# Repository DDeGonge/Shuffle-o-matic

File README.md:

# Shuffle-o-matic

Full overview video:
https://www.youtube.com/watch?v=eMTXyl7tPEk

Thingiverse page (cad files):
https://www.thingiverse.com/thing:4547302

## Significant experience recommended if you want to take on this project, it isn't documented very well :)

Hardware required
|Qty|Item|Supplier||
|---|---|---|---|
| | 3D printed Parts | |
| 3 | Nema 17 stepper motors, <=40mm long | [17HS15-1504S-X1 39mm long](https://www.aliexpress.com/item/1005002191787745.html?spm=2114.12010612.8148356.4.2bca2904n3VYBm)|
| 5 | Gates GT2 20t idlers with standoffs | |
| 3 | Gates GT2 20t drive pulleys | |
| 1 | MG90S servo | [MG90S servo](https://ebay.us/60Pxun) |
| 1 | 600rpm micro gearbox motor | [DC 3V 6V 12V GA12-N20](https://www.aliexpress.com/item/4000274747864.html?spm=a2g0o.productlist.0.0.63e42e07j3CYN8&algo_pvid=cd6ee419-621c-4ffe-9044-3ffd2ae1bfeb&algo_expid=cd6ee419-621c-4ffe-9044-3ffd2ae1bfeb-0&btsid=0bb0623a16150221042227975ecf2c&ws_ab_test=searchweb0_0,searchweb201602_,searchweb201603_)|
| 2 | MGN9 linear profile bearings, 135mm len | [MGN9C](https://www.aliexpress.com/item/32773296501.html?spm=a2g0o.cart.0.0.54873c00SIeLte&mp=1) |
| 1 | MGN9 linear profile bearing, 95mm len | [MGN9C](https://www.aliexpress.com/item/32773296501.html?spm=a2g0o.cart.0.0.54873c00SIeLte&mp=1) |
| 6 | 6700 bearing | [6700ZZ](https://www.aliexpress.com/item/32852057465.html?spm=a2g0o.cart.0.0.54873c00SIeLte&mp=1) |
| 1 | Raspberry Pi | |
| 1 | (optional) Raspberry Pi Camera V1.4 | |
| 1 | (optional) 3x 3mm white led | |
| 1 | Adafruit Feather | |
| 1 | Breadboard/pcb for laying out components | |
| ~ | Assorted M2 and M3 nuts and bolts | |

All part numbers in the pcb should be accurate, though again review and order at your own risk. Use KiCad to view/edit, it's free!

And probably a few other things I'm forgetting. Seriously if you want to make this, do so at your own risk. Review the cad model yourself and make sure you have everything accounted for! This is not a project for beginners!

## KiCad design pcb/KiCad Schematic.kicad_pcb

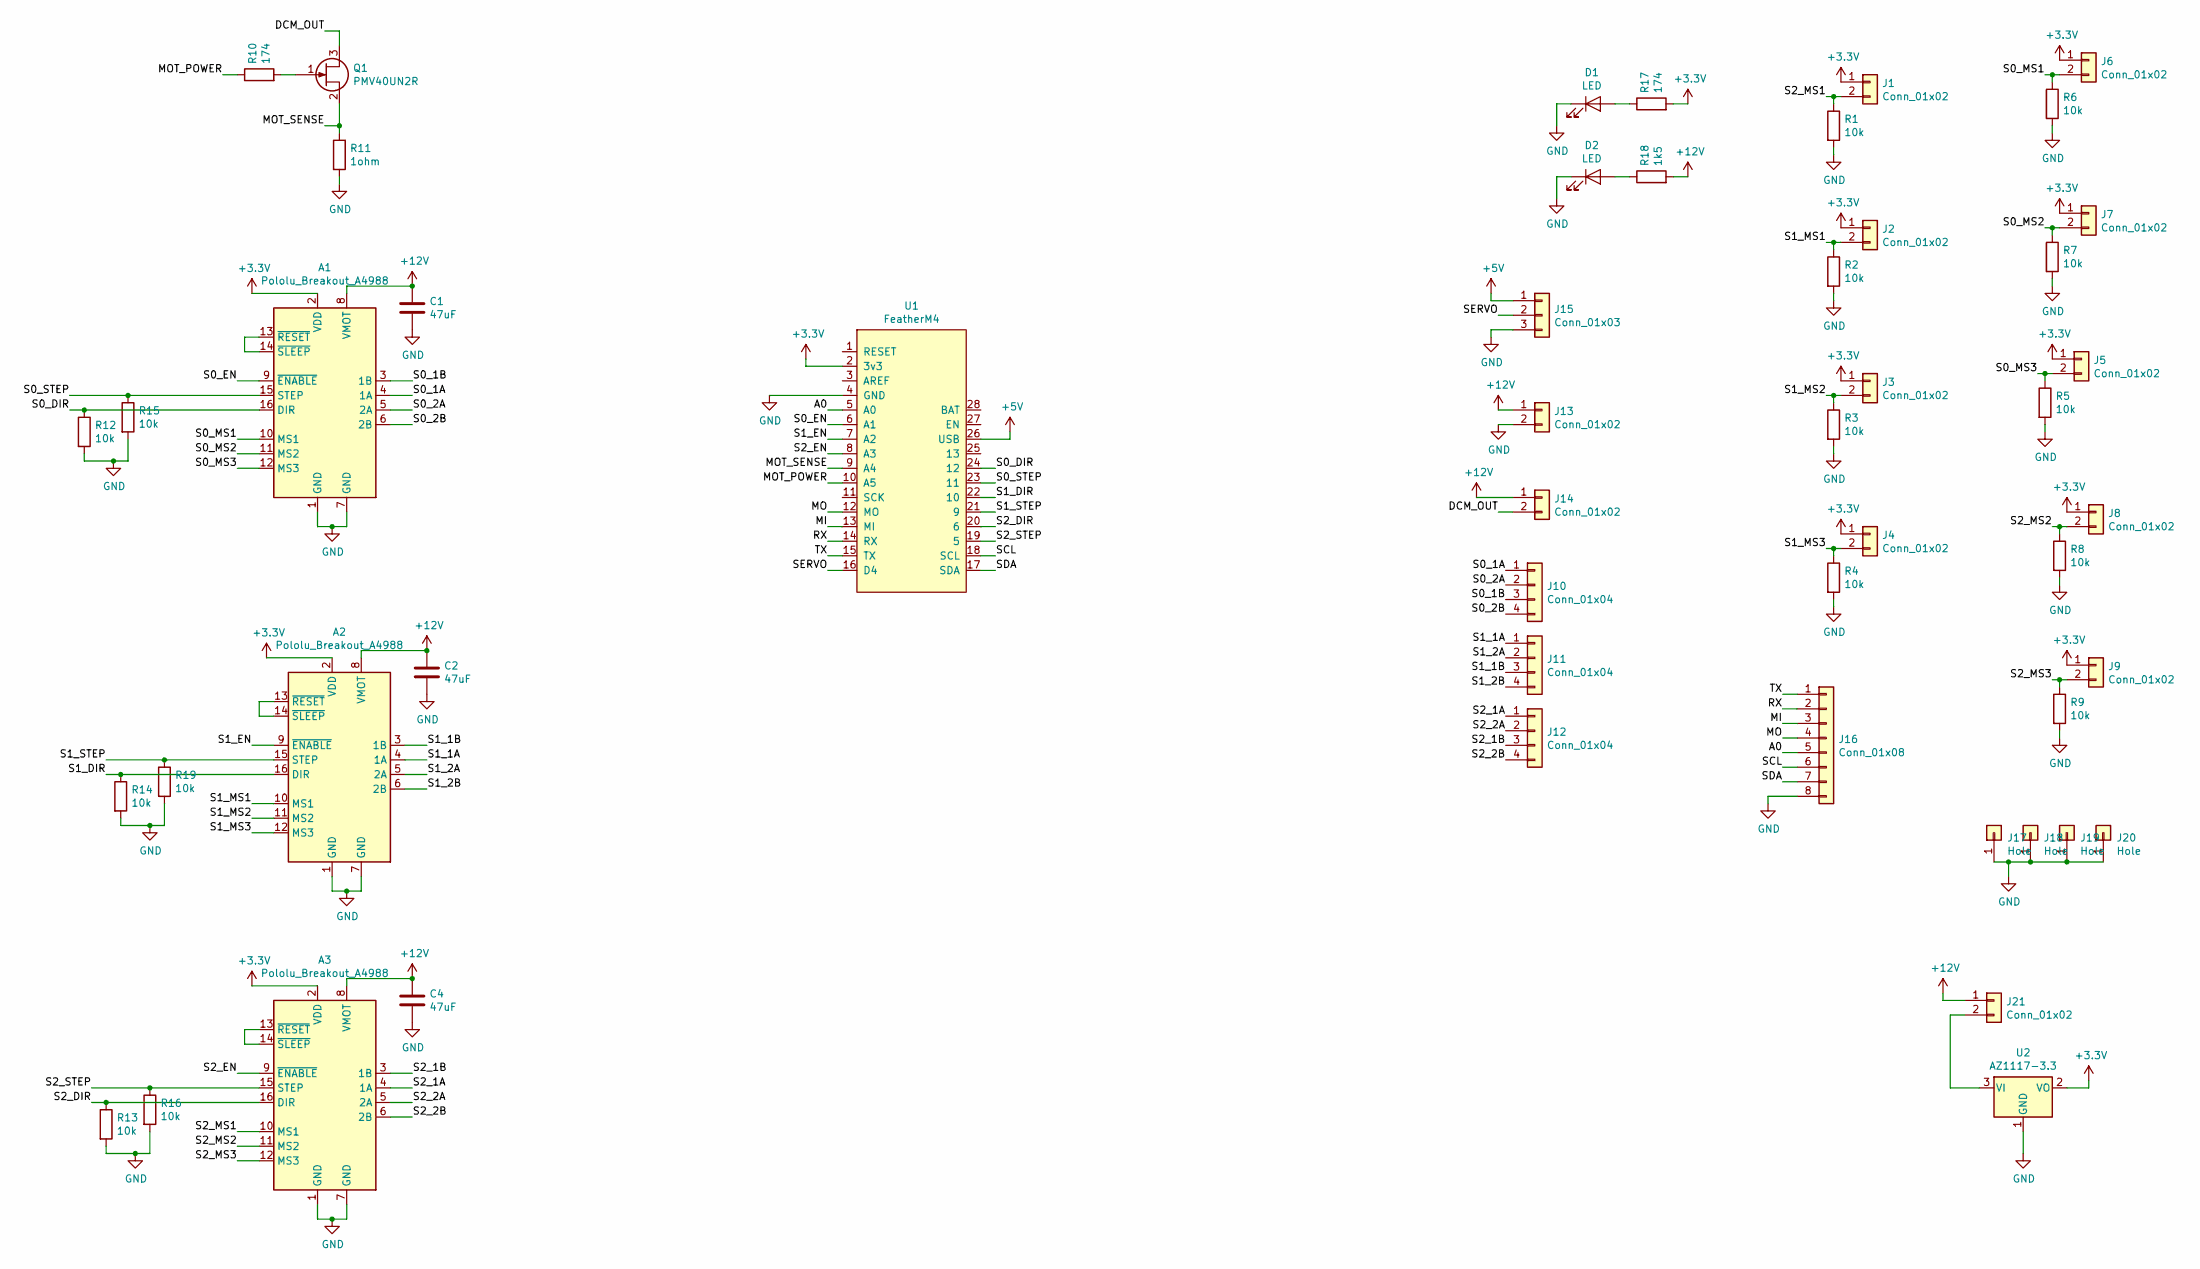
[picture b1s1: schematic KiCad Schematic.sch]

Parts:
A1, A2, A3: Pololu_Breakout_A4988; Pololu_Breakout-16_15.2x20.3mm
C1, C2, C4: 47uF; CP_Elec_6.3x5.8
D1, D2: LED; LED_0603_1608Metric
J1, J2, J3, J4, J5, J6, J7, J8, J9, J14, J21: Conn_01x02; PinHeader_1x02_P2.54mm_Vertical
J10, J11, J12: Conn_01x04; PinSocket_1x04_P2.54mm_Vertical
J13: Conn_01x02; BarrelJack_Wuerth_6941xx301002
J15: Conn_01x03; PinHeader_1x03_P2.54mm_Vertical
J16: Conn_01x08; PinHeader_1x08_P2.54mm_Vertical
J17, J18, J19, J20: Hole; MountingHole_2.7mm_M2.5_DIN965_Pad
Q1: PMV40UN2R; SOT-23
R1, R2, R3, R4, R5, R6, R7, R8, R9, R12, R13, R14, R15, R16, R19: 10k; R_0603_1608Metric
R10, R17: 174; R_0603_1608Metric
R11: 1ohm; R_0805_2012Metric
R18: 1k5; R_0603_1608Metric
U1: FeatherM4; FeatherFootprint
U2: AZ1117-3.3; SOT-223

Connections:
+3V3: A1.2 (VDD), A2.2 (VDD), A3.2 (VDD), J1.1, J2.1, J3.1, J4.1, J5.1, J6.1, J7.1, J8.1, J9.1, R17.2, U1.2 (3v3), U2.2 (VO)
+5V: J15.1, U1.26 (USB)
+12V: A1.8 (VMOT), A2.8 (VMOT), A3.8 (VMOT), C1.1, C2.1, C4.1, J13.1, J14.1, J21.1, R18.2
/A0: J16.5, U1.5 (A0)
/DCM_OUT: J14.2, Q1.3 (D)
/MI: J16.3, U1.13 (MI)
/MO: J16.4, U1.12 (MO)
/MOT_POWER: R10.1, U1.10 (A5)
/MOT_SENSE: Q1.2 (S), R11.1, U1.9 (A4)
/RX: J16.2, U1.14 (RX)
/S0_1A: A1.4 (1A), J10.1
/S0_1B: A1.3 (1B), J10.3
/S0_2A: A1.5 (2A), J10.2
/S0_2B: A1.6 (2B), J10.4
/S0_DIR: A1.16 (DIR), R12.1, U1.24 (12)
/S0_EN: A1.9 (~ENABLE), U1.6 (A1)
/S0_MS1: A1.10 (MS1), J6.2, R6.1
/S0_MS2: A1.11 (MS2), J7.2, R7.1
/S0_MS3: A1.12 (MS3), J5.2, R5.1
/S0_STEP: A1.15 (STEP), R15.1, U1.23 (11)
/S1_1A: A2.4 (1A), J11.1
/S1_1B: A2.3 (1B), J11.3
/S1_2A: A2.5 (2A), J11.2
/S1_2B: A2.6 (2B), J11.4
/S1_DIR: A2.16 (DIR), R14.1, U1.22 (10)
/S1_EN: A2.9 (~ENABLE), U1.7 (A2)
/S1_MS1: A2.10 (MS1), J2.2, R2.1
/S1_MS2: A2.11 (MS2), J3.2, R3.1
/S1_MS3: A2.12 (MS3), J4.2, R4.1
/S1_STEP: A2.15 (STEP), R19.1, U1.21 (9)
/S2_1A: A3.4 (1A), J12.1
/S2_1B: A3.3 (1B), J12.3
/S2_2A: A3.5 (2A), J12.2
/S2_2B: A3.6 (2B), J12.4
/S2_DIR: A3.16 (DIR), R13.1, U1.20 (6)
/S2_EN: A3.9 (~ENABLE), U1.8 (A3)
/S2_MS1: A3.10 (MS1), J1.2, R1.1
/S2_MS2: A3.11 (MS2), J8.2, R8.1
/S2_MS3: A3.12 (MS3), J9.2, R9.1
/S2_STEP: A3.15 (STEP), R16.1, U1.19 (5)
/SCL: J16.6, U1.18 (SCL)
/SDA: J16.7, U1.17 (SDA)
/SERVO: J15.2, U1.16 (D4)
/TX: J16.1, U1.15 (TX)
GND: A1.1 (GND), A1.7 (GND), A2.1 (GND), A2.7 (GND), A3.1 (GND), A3.7 (GND), C1.2, C2.2, C4.2, D1.1 (K), D2.1 (K), J13.2, J15.3, J16.8, J17.1, J18.1, J19.1, J20.1, R1.2, R2.2, R3.2, R4.2, R5.2, R6.2, R7.2, R8.2, R9.2, R11.2, R12.2, R13.2, R14.2, R15.2, R16.2, R19.2, U1.4 (GND), U2.1 (GND), U2.4
unnamed: A1.13 (~RESET), A1.14 (~SLEEP)
unnamed: A2.13 (~RESET), A2.14 (~SLEEP)
unnamed: A3.13 (~RESET), A3.14 (~SLEEP)
unnamed: D1.2 (A), R17.1
unnamed: D2.2 (A), R18.1
unnamed: J21.2, U2.3 (VI)
unnamed: Q1.1 (G), R10.2

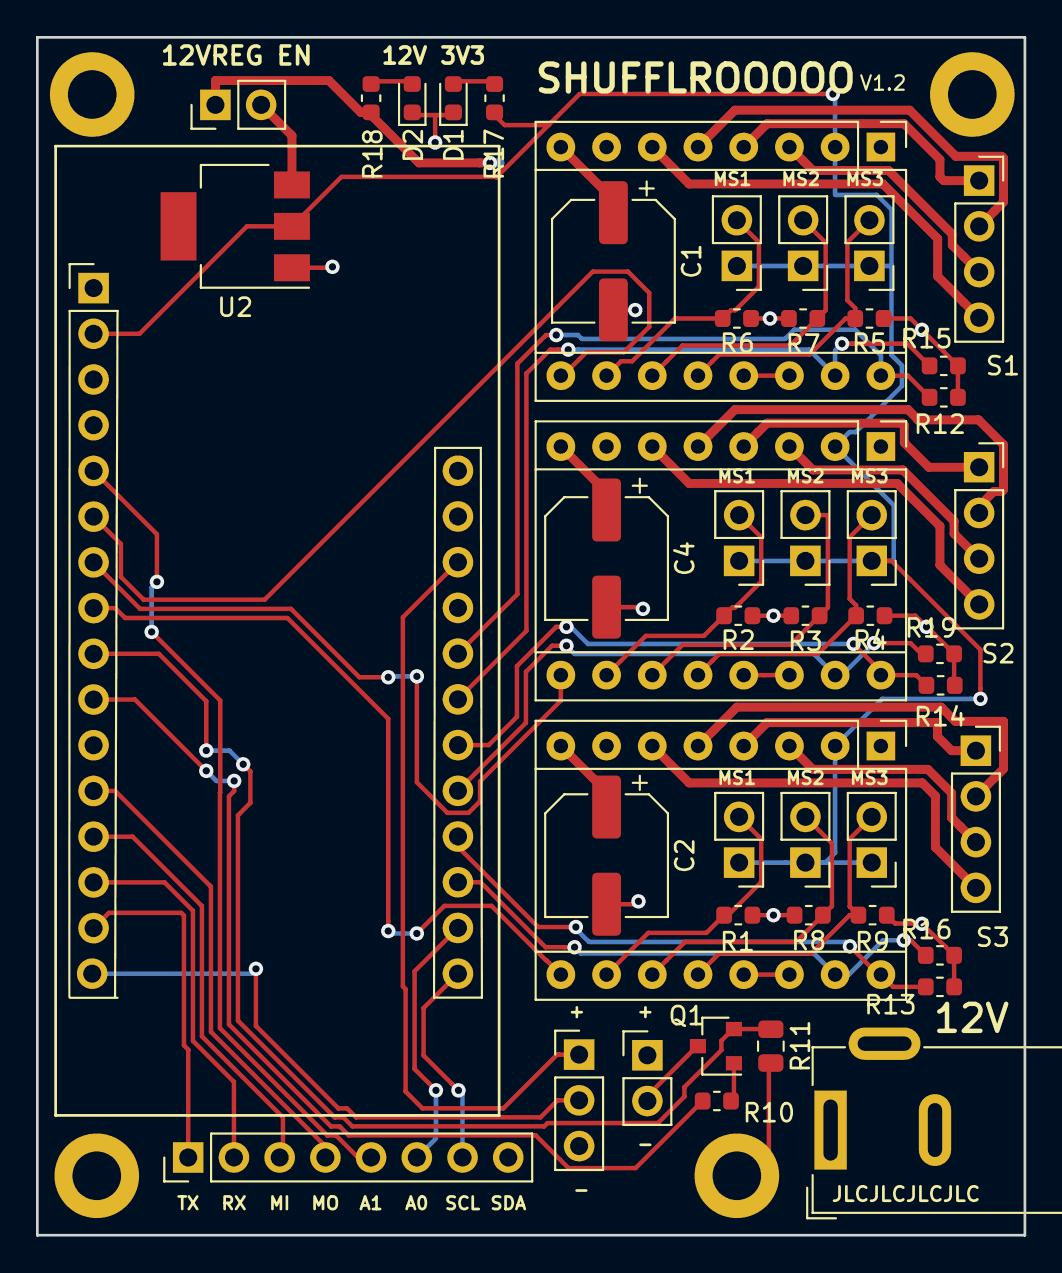
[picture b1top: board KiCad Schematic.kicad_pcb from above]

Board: 2 copper layers, 54.9 x 66.5 mm, 51 parts (0 on the bottom side), 52 nets.

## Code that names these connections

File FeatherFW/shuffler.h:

#include <Adafruit_NeoPixel.h>
#include <Servo.h>
#include <vector>
#include <algorithm>

#define servo_pin 4
#define dcmotor_power A5
#define dcmotor_sense A4

#define s0_en A1
#define s0_step 11
#define s0_dir 12
#define s1_en A2
#define s1_step 9
#define s1_dir 10
#define s2_en A3
#define s2_step 5
#define s2_dir 6

Adafruit_NeoPixel pixel = Adafruit_NeoPixel(1, 8, NEO_GRB + NEO_KHZ800);
Servo disp_servo;

using namespace std;

int cur_window_len = 20;
float cur_thresh_mult = 1.7;
int cur_baseline = 0;

struct stepper_obj
{
  public:
  void init(int s_pin, int d_pin, int e_pin, bool reverse);
  void enable();
  void disable();
  void set_dir(bool dir);
  void move_motor(int32_t s_target, int32_t v_max, int32_t accel);
  void overwrite_pos(int32_t newpos);
  void update_config(int32_t s_per_mm_new);
  int32_t get_pos();

  private:
  int step_pin;
  int dir_pin;
  int en_pin;
  int32_t pos;
  int8_t invert_dir;
  float steps_per_mm;
};

struct global_config
{
  public:
  uint16_t step_len_us;               // a
  uint8_t servo_min_pwm;              // b
  uint8_t servo_max_pwm;              // c
  uint16_t dispense_timeout_ms;       // d
  uint16_t current_detect_freq_hz;    // e
  uint16_t current_detect_window_ms;  // f
  float current_threshold_factor;     // g
  uint16_t servo_return_time_ms;      // h
  uint8_t dispense_max_attempts;      // i
};

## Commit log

2019-09-02 config file and better stuff
2019-09-03 motor routines and stuff
2019-09-05 tab fix
2019-09-05 update pin, fix function error
2019-10-25 implement relative move
2019-10-25 proper class inheritance
2019-10-28 rework motor driver
2019-10-28 fix tab error
2019-10-28 reorder driver list
2019-10-28 update pins
2019-10-28 default vel and acc for moves
2019-10-28 bugfix
2019-10-28 update pos reporting
2019-10-28 reduce pos_mm drift
2019-10-28 add debug mode
2019-10-28 add move time reporting
2019-10-28 change motor driver to use rpi.gpio
2019-10-28 limit switch and homing support
2019-10-28 remove auto home for motors
2019-11-03 add servo driver features
2019-11-09 driver updates
2019-11-09 servo driver update
2019-11-09 add servo destructor
2019-11-09 improve servo control
2019-11-09 add slow servo move
2019-11-09 revamp routines, dispense routine
2019-11-09 temp disable camera driver
2019-11-09 test servo dispense
2019-11-09 improve servo dispense routine
2019-11-10 shuffle architecture
2019-11-10 optimzations
2019-11-10 cfg tweaks
2020-01-05 add dc motor driver support, single direction
2020-01-05 enable dispense motor control in loop
2020-01-07 bugfix dcmotor driver
2020-04-06 convert code to use feather aux board for low level control
2020-04-18 refactor card detection
2020-04-18 add cam testing loop
2020-04-18 rearrage card detector files
2020-04-18 fix missing objects
2020-04-18 missing import
2020-04-19 camera stuff plus debugging
2020-04-19 add missing import
2020-04-19 clarificatoins
2020-04-19 attempt to bugfix camera
2020-04-19 replace scipy with PIL
2020-04-19 bugfixes
2020-04-19 tweak thresholds
2020-04-19 add more debugging pics
2020-04-19 fix cropping
2020-04-19 add debug lines and move debug image save
2020-04-19 stupid filepath bug fix
2020-04-19 repeated measurements and add error report
2020-04-19 make more lenient
2020-04-19 add input inversion
2020-04-19 debugging cropping
2020-04-19 add more debugging
2020-04-19 even more debuggin prints
2020-04-19 add contour trimming
2020-04-19 maybe this will fix contours
2020-04-19 try ignorant trimming
2020-04-19 contours suck
2020-04-19 maybe inverting first helps?
2020-04-19 getting ready for pi running feather
2020-04-19 update config and temp disable campera import cuz slow
2020-05-07 big changes for soldered pcb version
2020-05-24 working with custom pcb, add a bunch of features and improve speed and reliability
2020-06-15 working on web apps
2020-06-15 no clue what im doing
2020-06-15 finalize web architecture but still has bugs
2020-06-17 got webapp working and wip python communications
2020-06-17 bugfixes and progress - needs some refactoring
2020-06-17 blackjack implemented
2020-06-17 lots of progress, rand and bjack probably work now
2020-06-18 bugfixes and cleanup
2020-06-18 camera tweaks
2020-06-18 unify card detector names
2020-06-18 cfg updates and cal img name fixes
2020-06-18 bugfixes and tweaks
2020-06-19 card detection improvement attmept
2020-06-19 debug and tune card detection, update training images
2020-06-19 optimizations and way less jank code
2020-06-19 cleanup and begin work on holdem
2020-06-19 add exposure calibration help function
2020-06-19 camera stuff
2020-06-19 stuff
2020-06-21 add some debugging features
2020-06-21 camera bugfixes
2020-06-21 bugfixes, working with blackjack now
2020-06-21 more bugfixes
2020-06-21 first pass holdem processing
2020-06-22 in progress holdem deck arranging
2020-06-22 refactor holdem deck generation
2020-06-22 add more debugging info
2020-06-22 bug squishin
2020-06-25 only read card once and first try auto calibration
2020-06-25 add greyscale calibration offset
2020-06-25 deprecate CardDetector file, add better background cal offset, other improvements
2020-06-25 update cam filtering
2020-07-01 update to use dispenser stepper
2020-07-01 config update and minor bugfix
2020-07-01 config update
2020-07-06 update calibration images
2020-07-14 remove deprecated file, config tweaks, minor main loop optimizations
2020-07-15 buggies!
2020-07-15 final touches before first full test
2020-07-15 changes for video purposes
2020-07-15 fix import path
2020-07-17 improve reliability
2020-07-20 cleanup
2020-07-20 add pcb files
2021-03-06 docs: bom
2021-03-06 docs
2021-03-06 docs: fix Nema link to be for a product <= 40mm
2021-06-30 add main assembly step file
2021-10-23 Improving web UI: adding bootstrap to beautify and simplify styling, moving custom style to an external file, moving index file to PHP to generate some forms part, using selects instead of inputs wit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
